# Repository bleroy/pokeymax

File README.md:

# This repo is somewhat obsolete

I created this repo when Foft first released his design of the PokeyMax 4 board publicly.
I did so at the time because the design was still in Eagle format and somewhat difficult to keep track of.
I took the design, imported it to KiCad and published it here as a git repo.
I also took a stab at redesigning the board to bring the price down as much as possible (that's the 4s version of the board).

A lot has happened since.
Foft released multiple revisions of the board and HDL files, and quite a few people have built their own boards.
He's now using KiCad, so no more Eagle.
He also started working on a 4.5 revision as well as on several new designs, including the PokeyMin that uses a smaller FPGA version and resistors instead of level shifters.
That last design pretty much makes 4s obsolete and little more than a curiosity. For me, it was a nice exercise in designing such a small board.

In other words, nobody except maybe me should use the files on this repo. Instead, head over to Foft's site and download the latest files from there:
http://www.64kib.com/atarixlfpga_svn/trunk/atari_800xl/atari_chips/hardware/

# PokeyMax 4

Foft's public designs for PokeyMax.

Pokeys are getting rare and expensive. FPGA alternatives exist but are also expensive. Foft, the author of PokeyMax, has very generously made his designs public on [the AtariAge forums](https://forums.atariage.com/topic/364870-pokeymax-v4-bring-up-thread/).
With his permission, I'm publishing his latest iteration on PokeyMax, version 4, which is a 2-layer version with all components on the top side. This should be easier to produce at a lower cost than the previous versions. I've also imported the project in KiCad from the original Eagle files.

Foft has not specified a license for his work, but attribution should be maintained. This is his design, reproduced here under his permission.

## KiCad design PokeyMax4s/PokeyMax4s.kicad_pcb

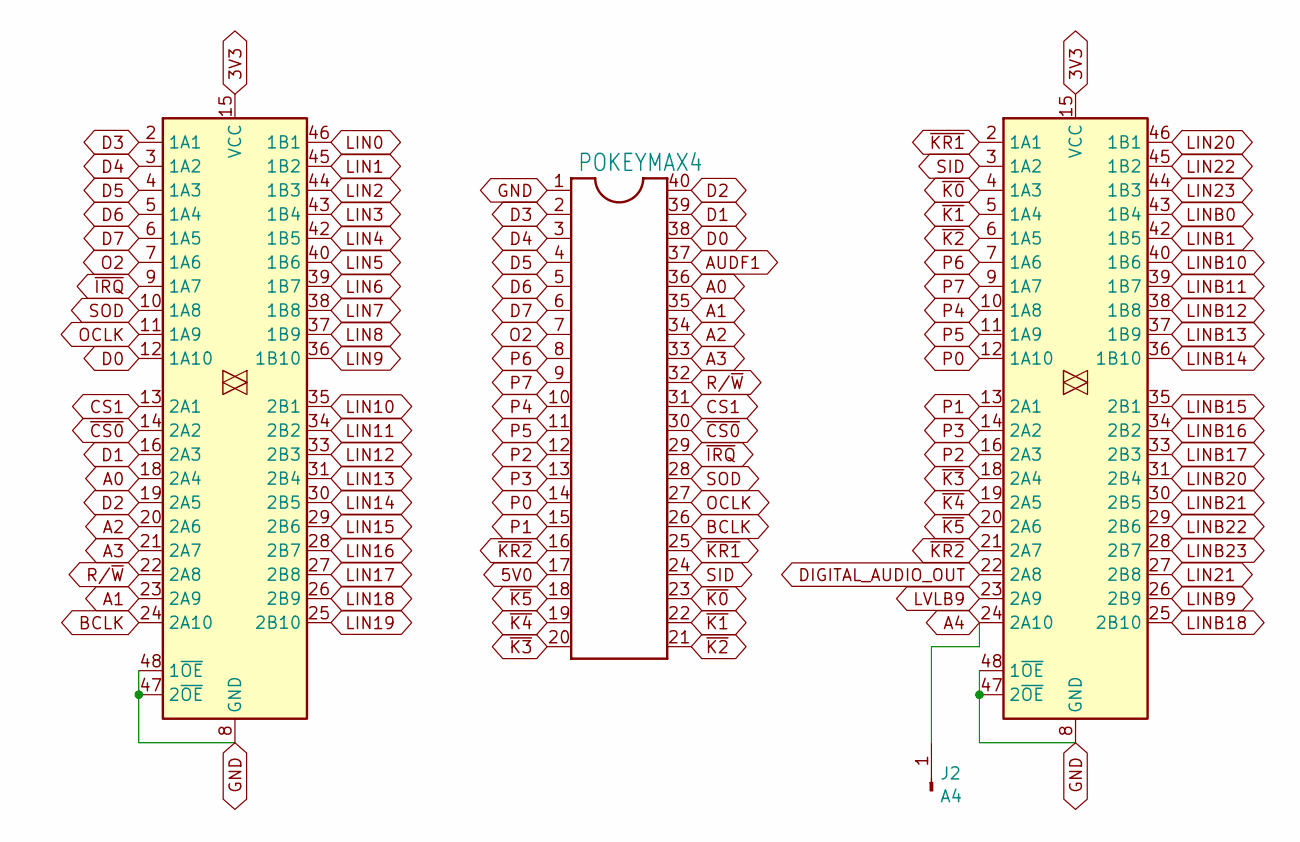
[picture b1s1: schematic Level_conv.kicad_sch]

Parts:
J2: A4; PinHeader_1x01_P2.54mm_Vertical
POKEYMAX4: DIL40; DIP-40_W15.24mm_Socket
U2, U4: 74CB3T16210; TSSOP-48_6.1x12.5mm_P0.5mm; LCSC Part # C2674635

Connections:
3V3: U2.15 (VCC), U4.15 (VCC); also elsewhere on the board
5V0: POKEYMAX4.17; also elsewhere on the board
A0: POKEYMAX4.36, U4.18 (2A4)
A1: POKEYMAX4.35, U4.23 (2A9)
A2: POKEYMAX4.34, U4.20 (2A6)
A3: POKEYMAX4.33, U4.21 (2A7)
A4: J2.1, U2.24 (2A10)
AUDF1: POKEYMAX4.37; also elsewhere on the board
BCLK: POKEYMAX4.26, U4.24 (2A10)
CS1: POKEYMAX4.31, U4.13 (2A1)
D0: POKEYMAX4.38, U4.12 (1A10)
D1: POKEYMAX4.39, U4.16 (2A3)
D2: POKEYMAX4.40, U4.19 (2A5)
D3: POKEYMAX4.2, U4.2 (1A1)
D4: POKEYMAX4.3, U4.3 (1A2)
D5: POKEYMAX4.4, U4.4 (1A3)
D6: POKEYMAX4.5, U4.5 (1A4)
D7: POKEYMAX4.6, U4.6 (1A5)
DIGITAL_AUDIO_OUT: U2.22 (2A8); also elsewhere on the board
GND: POKEYMAX4.1, U2.8 (GND), U2.17 (GND), U2.32 (GND), U2.41 (GND), U2.47 (2~OE), U2.48 (1~OE), U4.8 (GND), U4.17 (GND), U4.32 (GND), U4.41 (GND), U4.47 (2~OE), U4.48 (1~OE); also elsewhere on the board
LIN0: U4.46 (1B1); also elsewhere on the board
LIN1: U4.45 (1B2); also elsewhere on the board
LIN2: U4.44 (1B3); also elsewhere on the board
LIN3: U4.43 (1B4); also elsewhere on the board
LIN4: U4.42 (1B5); also elsewhere on the board
LIN5: U4.40 (1B6); also elsewhere on the board
LIN6: U4.39 (1B7); also elsewhere on the board
LIN7: U4.38 (1B8); also elsewhere on the board
LIN8: U4.37 (1B9); also elsewhere on the board
LIN9: U4.36 (1B10); also elsewhere on the board
LIN10: U4.35 (2B1); also elsewhere on the board
LIN11: U4.34 (2B2); also elsewhere on the board
LIN12: U4.33 (2B3); also elsewhere on the board
LIN13: U4.31 (2B4); also elsewhere on the board
LIN14: U4.30 (2B5); also elsewhere on the board
LIN15: U4.29 (2B6); also elsewhere on the board
LIN16: U4.28 (2B7); also elsewhere on the board
LIN17: U4.27 (2B8); also elsewhere on the board
LIN18: U4.26 (2B9); also elsewhere on the board
LIN19: U4.25 (2B10); also elsewhere on the board
LIN20: U2.46 (1B1); also elsewhere on the board
LIN21: U2.27 (2B8); also elsewhere on the board
LIN22: U2.45 (1B2); also elsewhere on the board
LIN23: U2.44 (1B3); also elsewhere on the board
LINB0: U2.43 (1B4); also elsewhere on the board
LINB1: U2.42 (1B5); also elsewhere on the board
LINB9: U2.26 (2B9); also elsewhere on the board
LINB10: U2.40 (1B6); also elsewhere on the board
LINB11: U2.39 (1B7); also elsewhere on the board
LINB12: U2.38 (1B8); also elsewhere on the board
LINB13: U2.37 (1B9); also elsewhere on the board
LINB14: U2.36 (1B10); also elsewhere on the board
LINB15: U2.35 (2B1); also elsewhere on the board
LINB16: U2.34 (2B2); also elsewhere on the board
LINB17: U2.33 (2B3); also elsewhere on the board
LINB18: U2.25 (2B10); also elsewhere on the board
LINB20: U2.31 (2B4); also elsewhere on the board
LINB21: U2.30 (2B5); also elsewhere on the board
LINB22: U2.29 (2B6); also elsewhere on the board
LINB23: U2.28 (2B7); also elsewhere on the board
LVLB9: U2.23 (2A9); also elsewhere on the board
O2: POKEYMAX4.7, U4.7 (1A6)
OCLK: POKEYMAX4.27, U4.11 (1A9)
P0: POKEYMAX4.14, U2.12 (1A10)
P1: POKEYMAX4.15, U2.13 (2A1)
P2: POKEYMAX4.12, U2.16 (2A3)
P3: POKEYMAX4.13, U2.14 (2A2)
P4: POKEYMAX4.10, U2.10 (1A8)
P5: POKEYMAX4.11, U2.11 (1A9)
P6: POKEYMAX4.8, U2.7 (1A6)
P7: POKEYMAX4.9, U2.9 (1A7)
R/~W: POKEYMAX4.32, U4.22 (2A8)
SID: POKEYMAX4.24, U2.3 (1A2)
SOD: POKEYMAX4.28, U4.10 (1A8)
~CS0: POKEYMAX4.30, U4.14 (2A2)
~IRQ: POKEYMAX4.29, U4.9 (1A7)
~K0: POKEYMAX4.23, U2.4 (1A3)
~K1: POKEYMAX4.22, U2.5 (1A4)
~K2: POKEYMAX4.21, U2.6 (1A5)
~K3: POKEYMAX4.20, U2.18 (2A4)
~K4: POKEYMAX4.19, U2.19 (2A5)
~K5: POKEYMAX4.18, U2.20 (2A6)
~KR1: POKEYMAX4.25, U2.2 (1A1)
~KR2: POKEYMAX4.16, U2.21 (2A7)

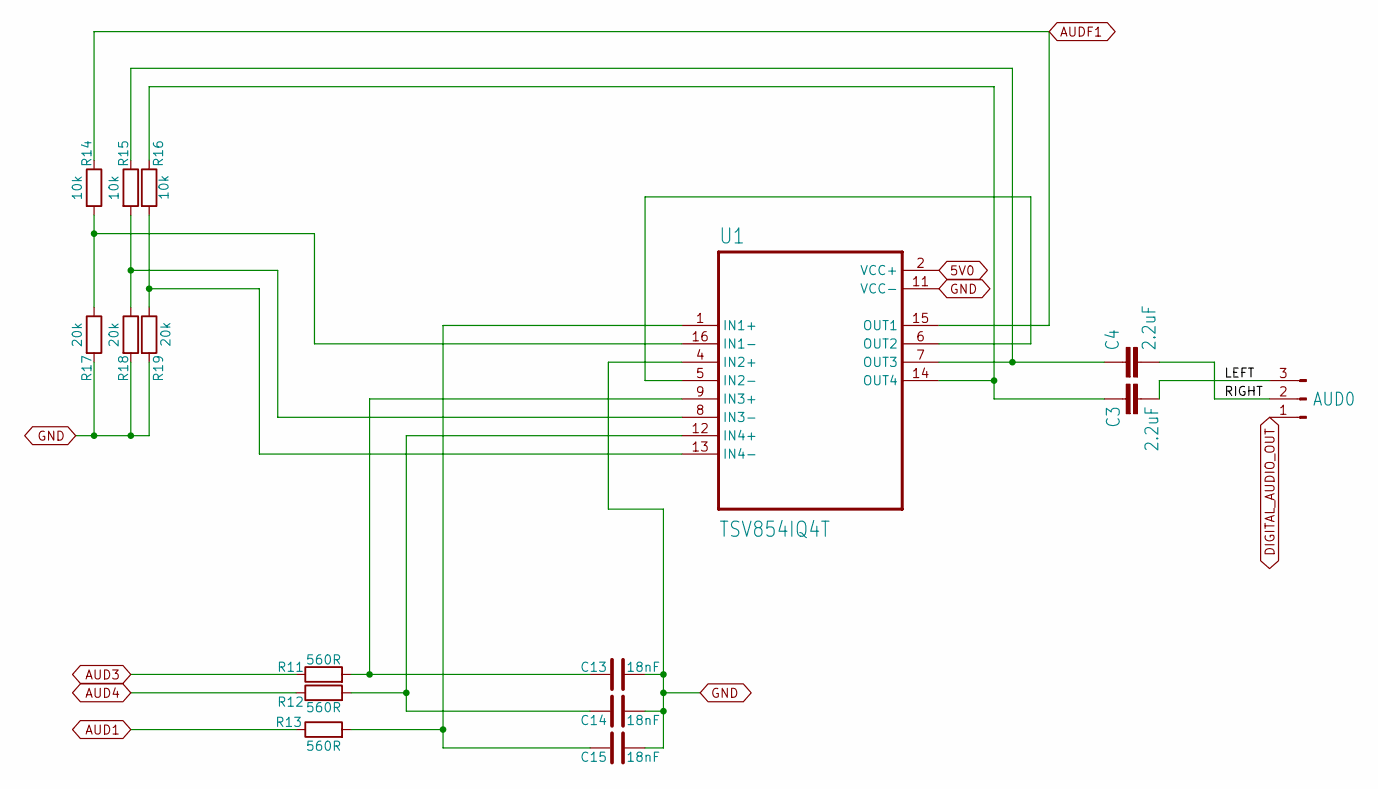
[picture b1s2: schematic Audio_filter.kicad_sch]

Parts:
AUD0: PINHD-2X2; PinHeader_1x03_P2.54mm_Vertical
C3, C4: 2.2uF; C_0402_1005Metric; LCSC Part # C12530
C13, C14, C15: 18nF; C_0402_1005Metric; LCSC Part # C576736
R11, R12, R13: 560R; R_0402_1005Metric; LCSC Part # C2909370
R14, R15, R16: 10k; R_0402_1005Metric; LCSC Part # C2906885
R17, R18, R19: 20k; R_0402_1005Metric; LCSC Part # C25545
U1: TSV854IQ4T; VQFN-16-1EP_3x3mm_P0.5mm_EP1.1x1.1mm; LCSC Part # C183029

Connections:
5V0: U1.2 (VCC+); also elsewhere on the board
/Audio filter/LEFT: AUD0.3, C3.2
/Audio filter/RIGHT: AUD0.2, C4.2
AUD1: R13.1; also elsewhere on the board
AUD3: R11.1; also elsewhere on the board
AUD4: R12.1; also elsewhere on the board
AUDF1: R14.1, U1.15 (OUT1); also elsewhere on the board
DIGITAL_AUDIO_OUT: AUD0.1; also elsewhere on the board
GND: C13.2, C14.2, C15.2, R17.2, R18.2, R19.2, U1.4 (IN2+), U1.11 (VCC-); also elsewhere on the board
unnamed: C15.1, R13.2, U1.1 (IN1+)
unnamed: R14.2, R17.1, U1.16 (IN1-)
unnamed: U1.5 (IN2-), U1.6 (OUT2)
unnamed: C13.1, R11.2, U1.9 (IN3+)
unnamed: R15.2, R18.1, U1.8 (IN3-)
unnamed: C14.1, R12.2, U1.12 (IN4+)
unnamed: R16.2, R19.1, U1.13 (IN4-)
unnamed: C4.1, R15.1, U1.7 (OUT3)
unnamed: C3.1, R16.1, U1.14 (OUT4)

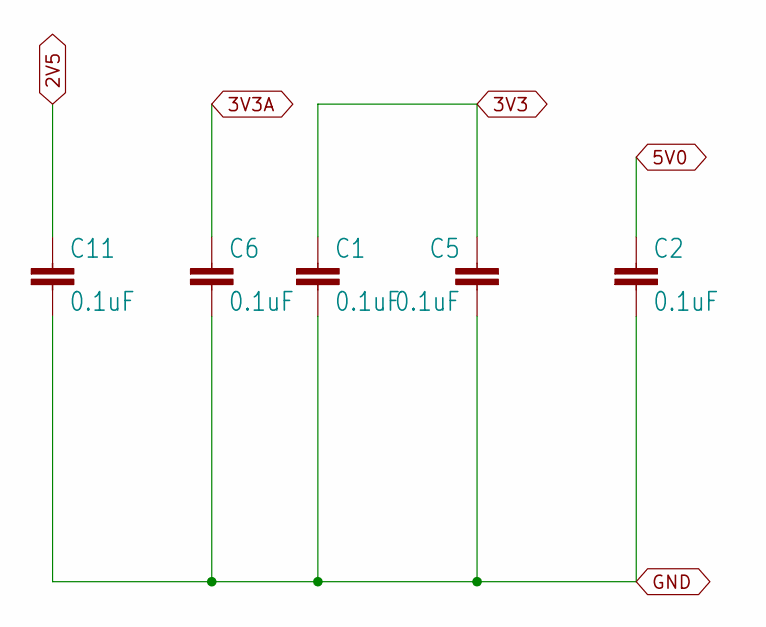
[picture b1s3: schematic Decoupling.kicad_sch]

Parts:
C1, C2, C5, C6, C11: 0.1uF; C_0402_1005Metric; LCSC Part # C60474

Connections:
2V5: C11.1; also elsewhere on the board
3V3: C1.1, C5.1; also elsewhere on the board
3V3A: C6.1; also elsewhere on the board
5V0: C2.1; also elsewhere on the board
GND: C1.2, C2.2, C5.2, C6.2, C11.2; also elsewhere on the board

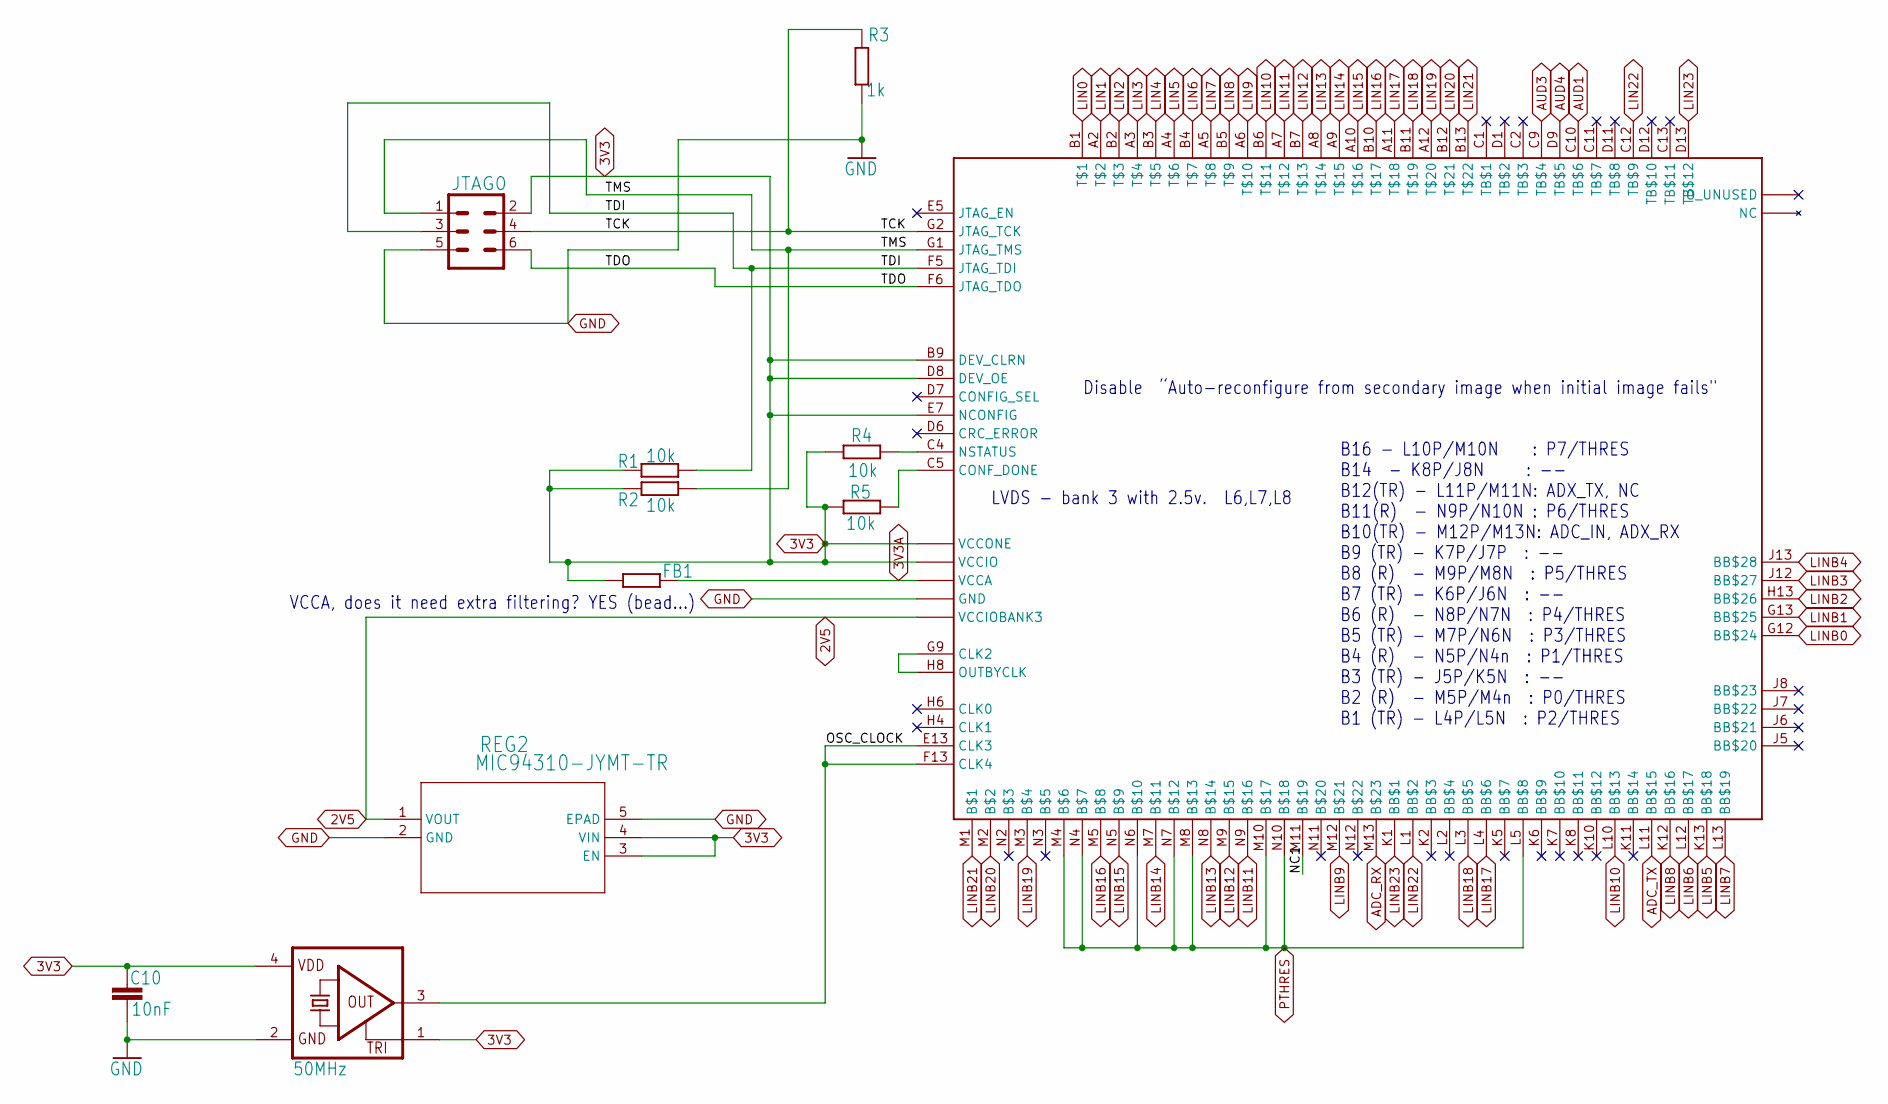
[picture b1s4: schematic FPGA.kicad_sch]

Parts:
C10: 10nF; C_0402_1005Metric; LCSC Part # C60133
FB1: R-EU_R0402; C_0402_1005Metric; LCSC Part # C160612
JTAG0: CONN_03X2LOCK; PinHeader_2x03_P2.54mm_Vertical
R1, R2, R4, R5: 10k; R_0402_1005Metric; LCSC Part # C2906885
R3: 1k; R_0402_1005Metric; LCSC Part # C2906899
REG2: MIC94310-JYMT-TR; TDFN4_1P2X1P6_MCH; LCSC Part # C622559
U3: MAX10; BGA-169_11.0x11.0mm_Layout13x13_P0.8mm_Ball0.5mm_Pad0.4mm_N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; LCSC Part # C1521844
X1: 50MHz; ASE; LCSC Part # C7431354

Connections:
2V5: REG2.1 (VOUT), U3.L6 (VCCIOBANK3), U3.L7 (VCCIOBANK3), U3.L8 (VCCIOBANK3); also elsewhere on the board
3V3: C10.1, FB1.1, JTAG0.2, R1.2, R2.2, R4.2, R5.1, REG2.3 (EN), REG2.4 (VIN), U3.B9 (DEV_CLRN), U3.C6 (VCCIO), U3.C7 (VCCIO), U3.C8 (VCCIO), U3.D8 (DEV_OE), U3.E7 (NCONFIG), U3.F2 (VCCIO), U3.F7 (VCCONE), U3.F11 (VCCIO), U3.G3 (VCCIO), U3.G6 (VCCONE), U3.G8 (VCCONE), U3.G11 (VCCIO), U3.H7 (VCCONE), U3.H11 (VCCIO), U3.J3 (VCCIO), U3.J11 (VCCIO), U3.K3 (VCCIO), X1.1 (TRI), X1.4 (VDD); also elsewhere on the board
3V3A: FB1.2, U3.D4 (VCCA), U3.D10 (VCCA), U3.K4 (VCCA), U3.K9 (VCCA); also elsewhere on the board
/FPGA/NC1: U3.M11
/FPGA/OSC_CLOCK: U3.E13 (CLK3), U3.F13 (CLK4), X1.3 (OUT)
/FPGA/TCK: JTAG0.4, R3.1, U3.G2 (JTAG_TCK)
/FPGA/TDI: JTAG0.3, R1.1, U3.F5 (JTAG_TDI)
/FPGA/TDO: JTAG0.6, U3.F6 (JTAG_TDO)
/FPGA/TMS: JTAG0.1, R2.1, U3.G1 (JTAG_TMS)
ADC_RX: U3.M13; also elsewhere on the board
ADC_TX: U3.L11 (BB$15); also elsewhere on the board
AUD1: U3.C10 (TB$6); also elsewhere on the board
AUD3: U3.C9 (TB$4); also elsewhere on the board
AUD4: U3.D9 (TB$5); also elsewhere on the board
GND: C10.2, JTAG0.5, R3.2, REG2.2 (GND), REG2.5 (EPAD), U3.A1 (GND), U3.A13 (GND), U3.B8 (GND), U3.C3 (GND), U3.D5 (GND), U3.E11 (GND), U3.F3 (GND), U3.G7 (GND), U3.H12 (GND), U3.J4 (GND), U3.L9 (GND), U3.M6 (GND), U3.N1 (GND), U3.N13 (GND), X1.2 (GND); also elsewhere on the board
LIN0: U3.B1; also elsewhere on the board
LIN1: U3.A2; also elsewhere on the board
LIN2: U3.B2; also elsewhere on the board
LIN3: U3.A3; also elsewhere on the board
LIN4: U3.B3; also elsewhere on the board
LIN5: U3.A4; also elsewhere on the board
LIN6: U3.B4; also elsewhere on the board
LIN7: U3.A5; also elsewhere on the board
LIN8: U3.B5; also elsewhere on the board
LIN9: U3.A6; also elsewhere on the board
LIN10: U3.B6; also elsewhere on the board
LIN11: U3.A7; also elsewhere on the board
LIN12: U3.B7; also elsewhere on the board
LIN13: U3.A8; also elsewhere on the board
LIN14: U3.A9; also elsewhere on the board
LIN15: U3.A10; also elsewhere on the board
LIN16: U3.B10; also elsewhere on the board
LIN17: U3.A11; also elsewhere on the board
LIN18: U3.B11; also elsewhere on the board
LIN19: U3.A12; also elsewhere on the board
LIN20: U3.B12; also elsewhere on the board
LIN21: U3.B13; also elsewhere on the board
LIN22: U3.C12 (TB$9); also elsewhere on the board
LIN23: U3.D13 (TB$12); also elsewhere on the board
LINB0: U3.G12 (BB$24); also elsewhere on the board
LINB1: U3.G13 (BB$25); also elsewhere on the board
LINB2: U3.H13 (BB$26)
LINB3: U3.J12 (BB$27)
LINB4: U3.J13 (BB$28)
LINB5: U3.K13 (BB$18)
LINB6: U3.L12 (BB$17)
LINB7: U3.L13 (BB$19)
LINB8: U3.K12 (BB$16)
LINB9: U3.M12; also elsewhere on the board
LINB10: U3.L10 (BB$13); also elsewhere on the board
LINB11: U3.N9; also elsewhere on the board
LINB12: U3.M9; also elsewhere on the board
LINB13: U3.N8; also elsewhere on the board
LINB14: U3.M7; also elsewhere on the board
LINB15: U3.N5; also elsewhere on the board
LINB16: U3.M5; also elsewhere on the board
LINB17: U3.L4 (BB$6); also elsewhere on the board
LINB18: U3.L3 (BB$5); also elsewhere on the board
LINB19: U3.M3
LINB20: U3.M2; also elsewhere on the board
LINB21: U3.M1; also elsewhere on the board
LINB22: U3.L1 (BB$2); also elsewhere on the board
LINB23: U3.K1 (BB$1); also elsewhere on the board
unnamed: U3.G9 (CLK2), U3.H8 (OUTBYCLK)
unnamed: R5.2, U3.C5 (CONF_DONE)
unnamed: R4.1, U3.C4 (NSTATUS)
PTHRES: U3.L5 (BB$8), U3.M4, U3.M8, U3.M10, U3.N4, U3.N6, U3.N7, U3.N10; also elsewhere on the board

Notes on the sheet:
Disable “Auto-reconfigure from secondary image when initial image fails"
B16 - L10P/M10N : P7/THRES B14 - K8P/J8N : -- B12(TR) - L11P/M11N: ADX_TX, NC B11(R) - N9P/N10N : P6/THRES B10(TR) - M12P/M13N: ADC_IN, ADX_RX B9 (TR) - K7P/J7P : -- B8 (R) - M9P/M8N : P5/THRES B7 (TR) - K6P/J6N : -- B6 (R) - N8P/N7N : P4/THRES B5 (TR) - M7P/N6N : P3/THRES B4 (R) - N5P/N4n : P1/THR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
LVDS - bank 3 with 2.5v. L6,L7,L8
VCCA, does it need extra filtering? YES (bead...)

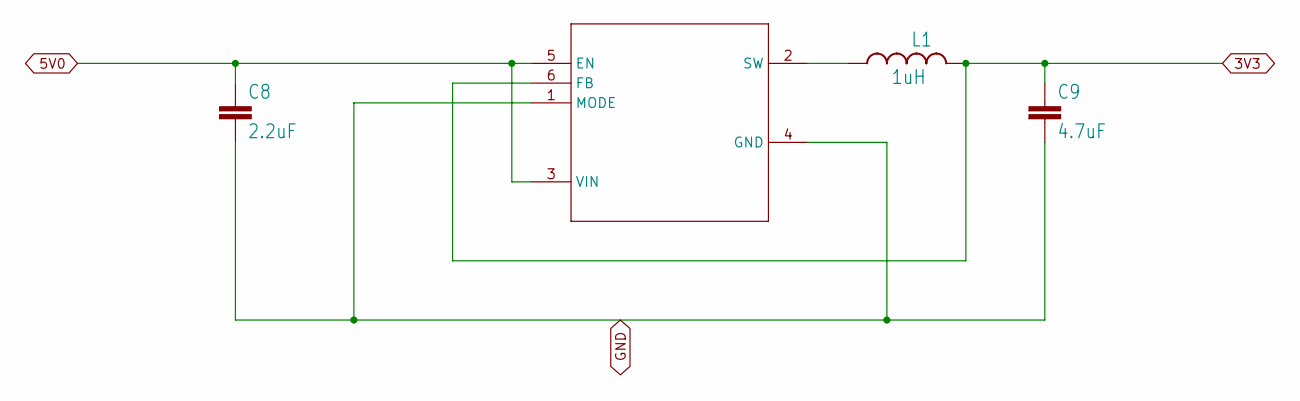
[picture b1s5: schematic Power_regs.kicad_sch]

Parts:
C8: 2.2uF; C_0402_1005Metric; LCSC Part # C12530
C9: 4.7uF; C_0402_1005Metric; LCSC Part # C307423
L1: 1uH; L_1206_3216Metric; LCSC Part # C139248
REG1: TPS62237DRYR; DRY6; LCSC Part # C398923

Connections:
3V3: C9.1, L1.2, REG1.6 (FB); also elsewhere on the board
5V0: C8.1, REG1.3 (VIN), REG1.5 (EN); also elsewhere on the board
GND: C8.2, C9.2, REG1.1 (MODE), REG1.4 (GND); also elsewhere on the board
unnamed: L1.1, REG1.2 (SW)

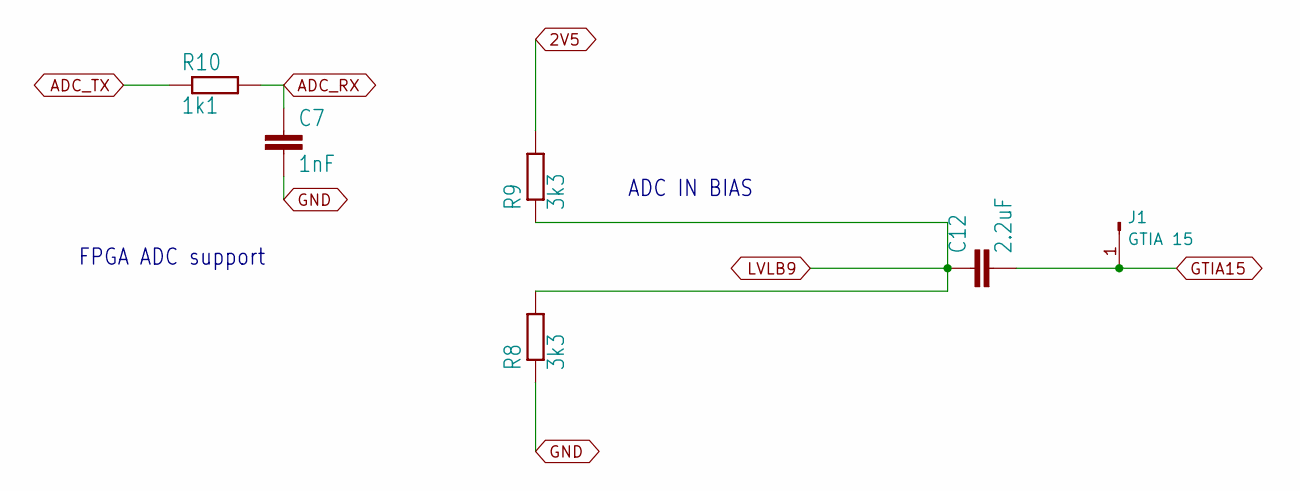
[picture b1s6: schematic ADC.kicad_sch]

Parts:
C7: 1nF; C_0402_1005Metric; LCSC Part # C106205
C12: 2.2uF; C_0402_1005Metric; LCSC Part # C12530
J1: GTIA 15; PinHeader_1x01_P2.54mm_Vertical
R8, R9: 3k3; R_0402_1005Metric; LCSC Part # C25936
R10: 1k1; R_0402_1005Metric; LCSC Part # C25860

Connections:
2V5: R9.2; also elsewhere on the board
ADC_RX: C7.1, R10.2; also elsewhere on the board
ADC_TX: R10.1; also elsewhere on the board
GND: C7.2, R8.1; also elsewhere on the board
GTIA15: C12.2, J1.1
LVLB9: C12.1, R8.2, R9.1; also elsewhere on the board

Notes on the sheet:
ADC IN BIAS
FPGA ADC support

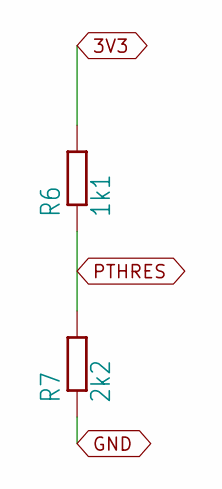
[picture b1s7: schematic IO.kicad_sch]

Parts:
R6: 1k1; R_0402_1005Metric; LCSC Part # C25860
R7: 2k2; R_0402_1005Metric; LCSC Part # C25933

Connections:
3V3: R6.2; also elsewhere on the board
GND: R7.1; also elsewhere on the board
PTHRES: R6.1, R7.2; also elsewhere on the board

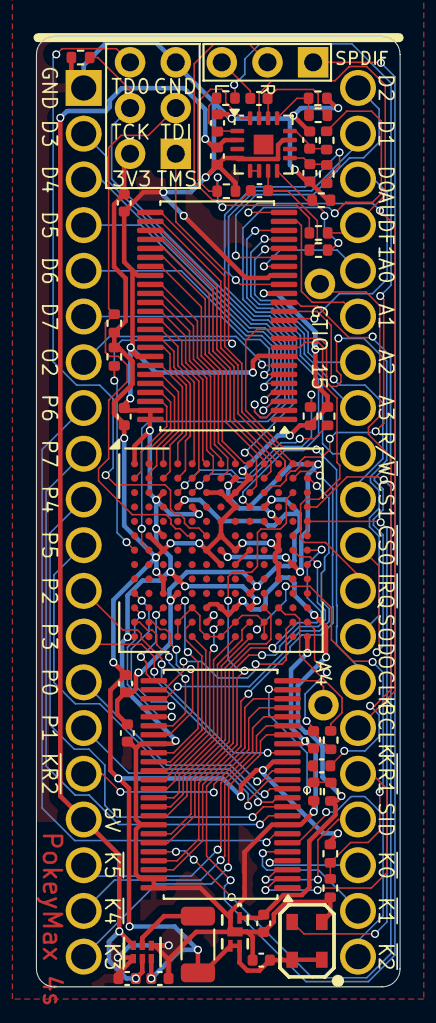
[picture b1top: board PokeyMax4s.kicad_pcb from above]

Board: 2 copper layers, 20.2 x 52.8 mm, 48 parts (0 on the bottom side), 113 nets.

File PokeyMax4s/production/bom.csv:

Designator,Footprint,Quantity,Value,LCSC Part #
"C1, C11, C2, C5, C6",0402,5,0.1uF,C60474
C10,0402,1,10nF,C60133
"C12, C3, C4, C8",0402,4,2.2uF,C12530
"C13, C14, C15",0402,3,18nF,C576736
C7,0402,1,1nF,C106205
C9,0402,1,4.7uF,C307423
FB1,0402,1,R-EU_R0402,C160612
L1,1206,1,1uH,C139248
"R1, R14, R15, R16, R2, R4, R5",0402,7,10k,C2906885
"R10, R6",0402,2,1k1,C25860
"R11, R12, R13",0402,3,560R,C2909370
"R17, R18, R19",0402,3,20k,C25545
R3,0402,1,1k,C2906899
R7,0402,1,2k2,C25933
"R8, R9",0402,2,3k3,C25936
REG1,DRY6,1,TPS62237DRYR,C398923
REG2,TDFN4_1P2X1P6_MCH,1,MIC94310-JYMT-TR,C622559
U1,VQFN-16-1EP_3x3mm_P0.5mm_EP1.1x1.1mm,1,TSV854IQ4T,C183029
"U2, U4",TSSOP-48_6.1x12.5mm_P0.5mm,2,74CB3T16210,C2674635
U3,BGA-169_11.0x11.0mm_Layout13x13_P0.8mm_Ball0.5mm_Pad0.4mm_NSMD,1,MAX10,C1521844
X1,ASE,1,50MHz,C7431354

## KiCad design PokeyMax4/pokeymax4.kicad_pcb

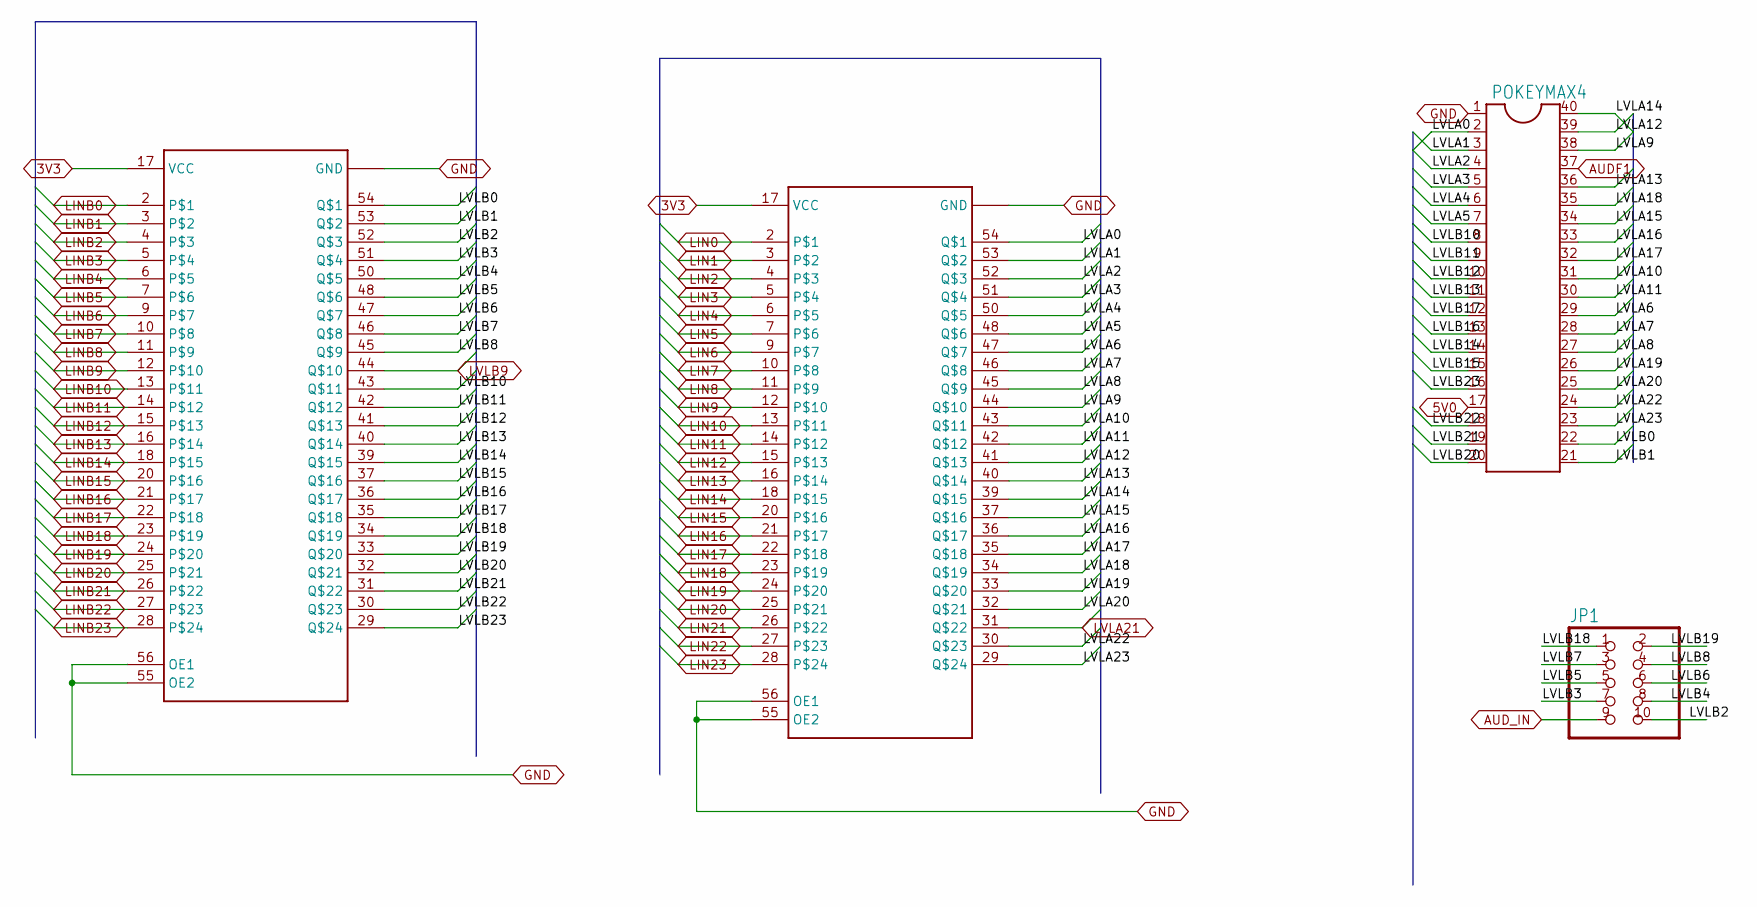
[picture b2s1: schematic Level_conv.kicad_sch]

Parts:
JP1: PINHD-2X5; 2X05
POKEYMAX4: DIL40
U2, U4: SN74CB3T16211SM; 56TVSOP_SMALL; LCSC Part # C2674751

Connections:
3V3: U2.17 (VCC), U4.17 (VCC); also elsewhere on the board
5V0: POKEYMAX4.17; also elsewhere on the board
/Level conv/LVLA0: POKEYMAX4.2, U2.54
/Level conv/LVLA1: POKEYMAX4.3, U2.53
/Level conv/LVLA2: POKEYMAX4.4, U2.52
/Level conv/LVLA3: POKEYMAX4.5, U2.51
/Level conv/LVLA4: POKEYMAX4.6, U2.50
/Level conv/LVLA5: POKEYMAX4.7, U2.48
/Level conv/LVLA6: POKEYMAX4.29, U2.47
/Level conv/LVLA7: POKEYMAX4.28, U2.46
/Level conv/LVLA8: POKEYMAX4.27, U2.45
/Level conv/LVLA9: POKEYMAX4.38, U2.44
/Level conv/LVLA10: POKEYMAX4.31, U2.43
/Level conv/LVLA11: POKEYMAX4.30, U2.42
/Level conv/LVLA12: POKEYMAX4.39, U2.41
/Level conv/LVLA13: POKEYMAX4.36, U2.40
/Level conv/LVLA14: POKEYMAX4.40, U2.39
/Level conv/LVLA15: POKEYMAX4.34, U2.37
/Level conv/LVLA16: POKEYMAX4.33, U2.36
/Level conv/LVLA17: POKEYMAX4.32, U2.35
/Level conv/LVLA18: POKEYMAX4.35, U2.34
/Level conv/LVLA19: POKEYMAX4.26, U2.33
/Level conv/LVLA20: POKEYMAX4.25, U2.32
/Level conv/LVLA22: POKEYMAX4.24, U2.30
/Level conv/LVLA23: POKEYMAX4.23, U2.29
/Level conv/LVLB0: POKEYMAX4.22, U4.54
/Level conv/LVLB1: POKEYMAX4.21, U4.53
/Level conv/LVLB2: JP1.10, U4.52
/Level conv/LVLB3: JP1.7, U4.51
/Level conv/LVLB4: JP1.8, U4.50
/Level conv/LVLB5: JP1.5, U4.48
/Level conv/LVLB6: JP1.6, U4.47
/Level conv/LVLB7: JP1.3, U4.46
/Level conv/LVLB8: JP1.4, U4.45
/Level conv/LVLB10: POKEYMAX4.8, U4.43
/Level conv/LVLB11: POKEYMAX4.9, U4.42
/Level conv/LVLB12: POKEYMAX4.10, U4.41
/Level conv/LVLB13: POKEYMAX4.11, U4.40
/Level conv/LVLB14: POKEYMAX4.14, U4.39
/Level conv/LVLB15: POKEYMAX4.15, U4.37
/Level conv/LVLB16: POKEYMAX4.13, U4.36
/Level conv/LVLB17: POKEYMAX4.12, U4.35
/Level conv/LVLB18: JP1.1, U4.34
/Level conv/LVLB19: JP1.2, U4.33
/Level conv/LVLB20: POKEYMAX4.20, U4.32
/Level conv/LVLB21: POKEYMAX4.19, U4.31
/Level conv/LVLB22: POKEYMAX4.18, U4.30
/Level conv/LVLB23: POKEYMAX4.16, U4.29
AUDF1: POKEYMAX4.37; also elsewhere on the board
AUD_IN: JP1.9; also elsewhere on the board
GND: POKEYMAX4.1, U2.8 (GND), U2.19 (GND), U2.38 (GND), U2.49 (GND), U2.55 (OE2), U2.56 (OE1), U4.8 (GND), U4.19 (GND), U4.38 (GND), U4.49 (GND), U4.55 (OE2), U4.56 (OE1); also elsewhere on the board
LIN0: U2.2; also elsewhere on the board
LIN1: U2.3; also elsewhere on the board
LIN2: U2.4; also elsewhere on the board
LIN3: U2.5; also elsewhere on the board
LIN4: U2.6; also elsewhere on the board
LIN5: U2.7; also elsewhere on the board
LIN6: U2.9; also elsewhere on the board
LIN7: U2.10; also elsewhere on the board
LIN8: U2.11; also elsewhere on the board
LIN9: U2.12; also elsewhere on the board
LIN10: U2.13; also elsewhere on the board
LIN11: U2.14; also elsewhere on the board
LIN12: U2.15; also elsewhere on the board
LIN13: U2.16; also elsewhere on the board
LIN14: U2.18; also elsewhere on the board
LIN15: U2.20; also elsewhere on the board
LIN16: U2.21; also elsewhere on the board
LIN17: U2.22; also elsewhere on the board
LIN18: U2.23; also elsewhere on the board
LIN19: U2.24; also elsewhere on the board
LIN20: U2.25; also elsewhere on the board
LIN21: U2.26; also elsewhere on the board
LIN22: U2.27; also elsewhere on the board
LIN23: U2.28; also elsewhere on the board
LINB0: U4.2; also elsewhere on the board
LINB1: U4.3; also elsewhere on the board
LINB2: U4.4; also elsewhere on the board
LINB3: U4.5; also elsewhere on the board
LINB4: U4.6; also elsewhere on the board
LINB5: U4.7; also elsewhere on the board
LINB6: U4.9; also elsewhere on the board
LINB7: U4.10; also elsewhere on the board
LINB8: U4.11; also elsewhere on the board
LINB9: U4.12; also elsewhere on the board
LINB10: U4.13; also elsewhere on the board
LINB11: U4.14; also elsewhere on the board
LINB12: U4.15; also elsewhere on the board
LINB13: U4.16; also elsewhere on the board
LINB14: U4.18; also elsewhere on the board
LINB15: U4.20; also elsewhere on the board
LINB16: U4.21; also elsewhere on the board
LINB17: U4.22; also elsewhere on the board
LINB18: U4.23; also elsewhere on the board
LINB19: U4.24; also elsewhere on the board
LINB20: U4.25; also elsewhere on the board
LINB21: U4.26; also elsewhere on the board
LINB22: U4.27; also elsewhere on the board
LINB23: U4.28; also elsewhere on the board
LVLA21: U2.31; also elsewhere on the board
LVLB9: U4.44; also elsewhere on the board

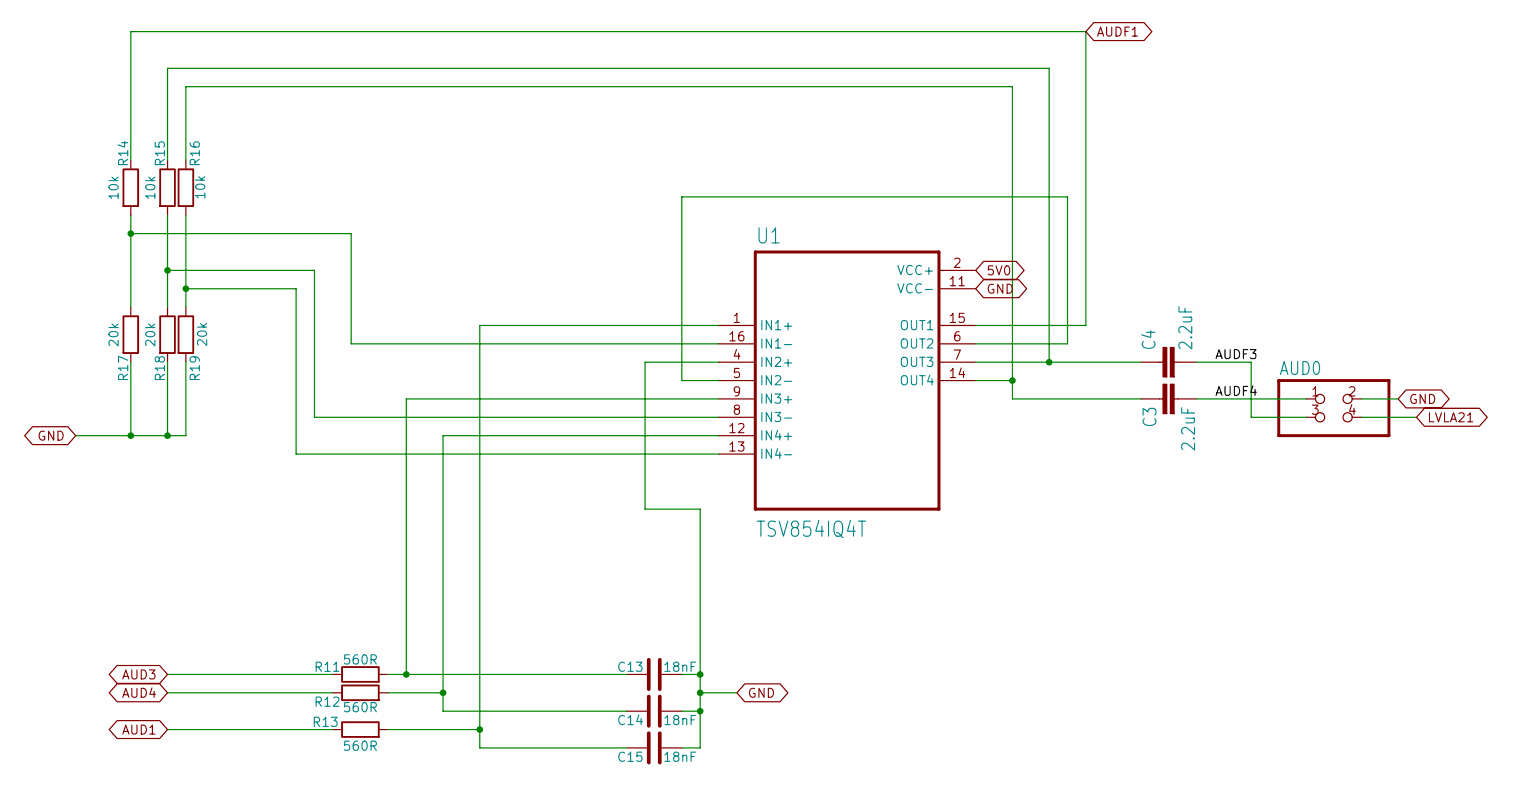
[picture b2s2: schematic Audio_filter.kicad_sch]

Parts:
AUD0: PINHD-2X2; 2X02
C3, C4: 2.2uF; C0402; LCSC Part # C43922
C13, C14, C15: 18nF; C0402; LCSC Part # C107079
R11, R12, R13: 560R; R_0402_1005Metric
R14, R15, R16: 10k; R_0402_1005Metric
R17, R18, R19: 20k; R_0402_1005Metric
U1: TSV854IQ4T; QFN50P300X300X100-16N; LCSC Part # C2058240

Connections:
5V0: U1.2 (VCC+); also elsewhere on the board
/Audio filter/AUDF3: AUD0.3, C4.2
/Audio filter/AUDF4: AUD0.1, C3.2
AUD1: R13.1; also elsewhere on the board
AUD3: R11.1; also elsewhere on the board
AUD4: R12.1; also elsewhere on the board
AUDF1: R14.1, U1.15 (OUT1); also elsewhere on the board
GND: AUD0.2, C13.2, C14.2, C15.2, R17.2, R18.2, R19.2, U1.4 (IN2+), U1.11 (VCC-); also elsewhere on the board
LVLA21: AUD0.4; also elsewhere on the board
unnamed: C15.1, R13.2, U1.1 (IN1+)
unnamed: R14.2, R17.1, U1.16 (IN1-)
unnamed: U1.5 (IN2-), U1.6 (OUT2)
unnamed: C13.1, R11.2, U1.9 (IN3+)
unnamed: R15.2, R18.1, U1.8 (IN3-)
unnamed: C14.1, R12.2, U1.12 (IN4+)
unnamed: R16.2, R19.1, U1.13 (IN4-)
unnamed: C4.1, R15.1, U1.7 (OUT3)
unnamed: C3.1, R16.1, U1.14 (OUT4)

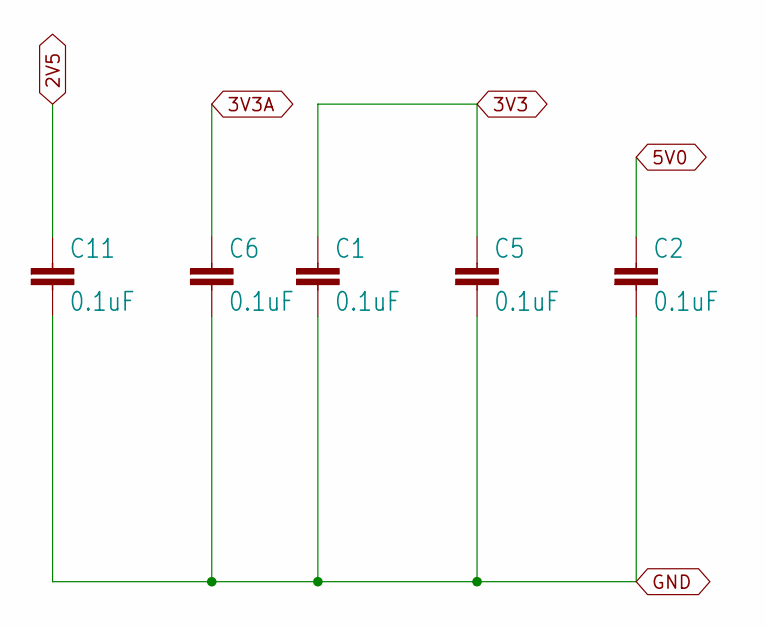
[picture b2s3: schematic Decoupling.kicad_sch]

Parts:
C1, C2, C5, C6, C11: 0.1uF; C0402; LCSC Part # C88219

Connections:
2V5: C11.1; also elsewhere on the board
3V3: C1.1, C5.1; also elsewhere on the board
3V3A: C6.1; also elsewhere on the board
5V0: C2.1; also elsewhere on the board
GND: C1.2, C2.2, C5.2, C6.2, C11.2; also elsewhere on the board

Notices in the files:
VHDL/pokeymax.qsf:
Copyright (C) 2017  Intel Corporation. All rights reserved.
